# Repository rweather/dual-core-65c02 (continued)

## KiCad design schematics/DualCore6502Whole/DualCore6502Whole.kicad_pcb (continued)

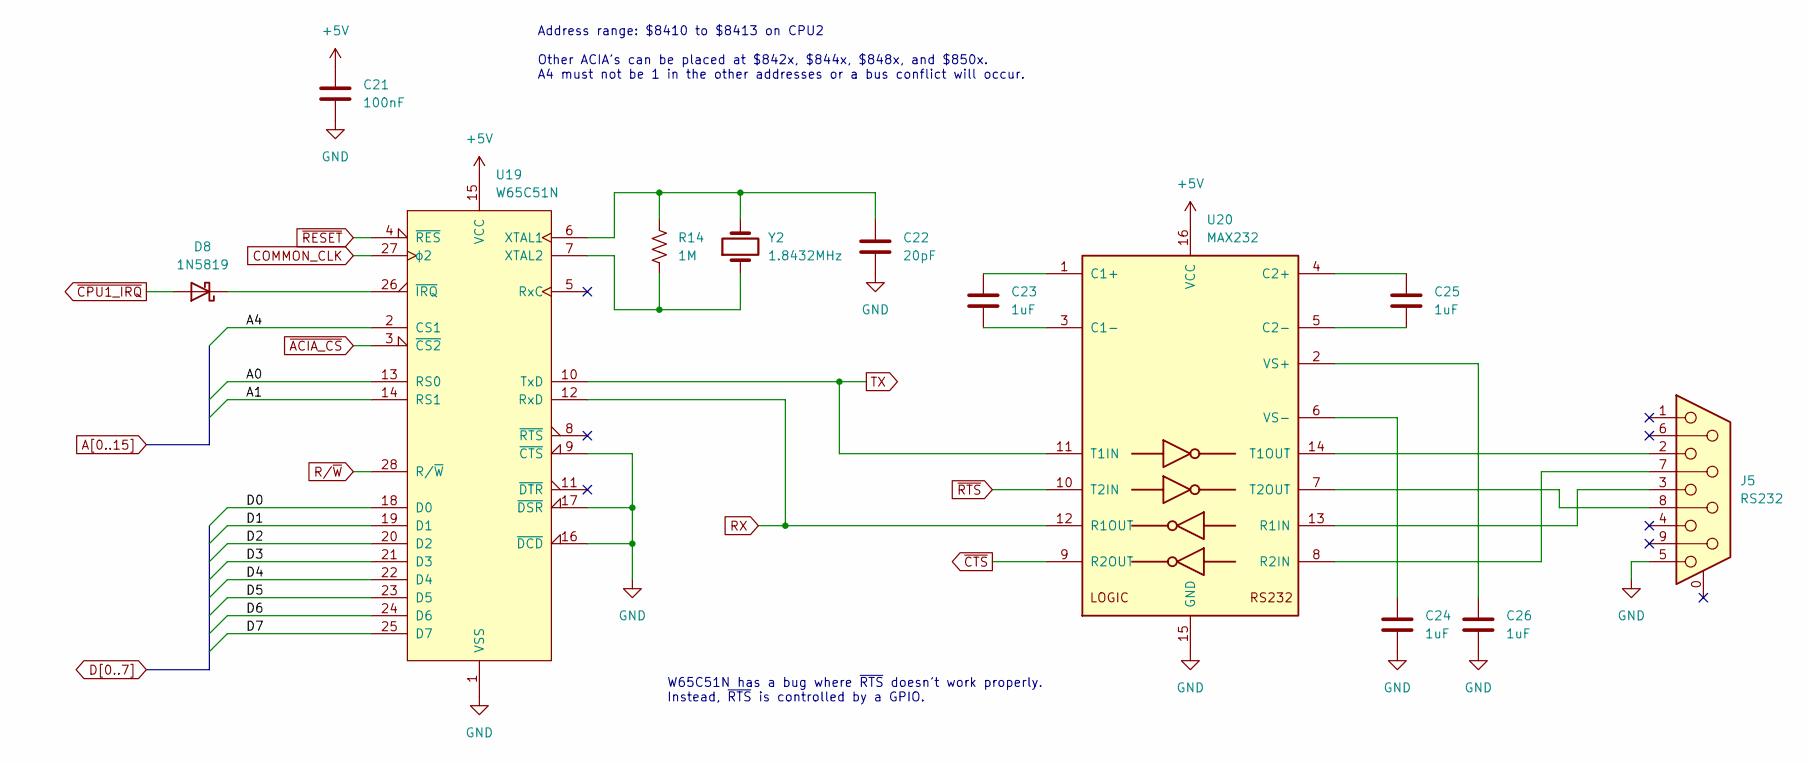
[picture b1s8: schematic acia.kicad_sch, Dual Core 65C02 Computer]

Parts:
C21: 100nF; C_Disc_D5.0mm_W2.5mm_P5.00mm
C22: 20pF; C_Disc_D5.0mm_W2.5mm_P5.00mm
C23, C24, C25, C26: 1uF; C_Disc_D5.0mm_W2.5mm_P5.00mm
D8: 1N5819; D_DO-41_SOD81_P10.16mm_Horizontal
J5: RS232; DSUB-9_Female_Horizontal_P2.77x2.84mm_EdgePinOffset4.94mm_H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
R14: 1M; R_Axial_DIN0207_L6.3mm_D2.5mm_P10.16mm_Horizontal
U19: W65C51N; DIP-28_W15.24mm_Socket
U20: MAX232; DIP-16_W7.62mm_Socket
Y2: 1.8432MHz; Crystal_HC49-U_Vertical

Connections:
+5V: C21.1, U19.15 (VCC), U20.16 (VCC); also elsewhere on the board
A0: U19.13 (RS0); also elsewhere on the board
A1: U19.14 (RS1); also elsewhere on the board
A4: U19.2 (CS1); also elsewhere on the board
COMMON_CLK: U19.27 (ϕ2); also elsewhere on the board
D0: U19.18 (D0); also elsewhere on the board
D1: U19.19 (D1); also elsewhere on the board
D2: U19.20 (D2); also elsewhere on the board
D3: U19.21 (D3); also elsewhere on the board
D4: U19.22 (D4); also elsewhere on the board
D5: U19.23 (D5); also elsewhere on the board
D6: U19.24 (D6); also elsewhere on the board
D7: U19.25 (D7); also elsewhere on the board
GND: C21.2, C22.2, C24.2, C26.2, J5.5, U19.1 (VSS), U19.9 (~CTS), U19.16 (~DCD), U19.17 (~DSR), U20.15 (GND); also elsewhere on the board
unnamed: D8.1 (K), U19.26 (~IRQ)
unnamed: C22.1, R14.1, U19.6 (XTAL1), Y2.2
unnamed: R14.2, U19.7 (XTAL2), Y2.1
unnamed: C23.1, U20.1 (C1+)
unnamed: C23.2, U20.3 (C1-)
unnamed: C25.1, U20.4 (C2+)
unnamed: C25.2, U20.5 (C2-)
unnamed: J5.3, U20.13 (R1IN)
unnamed: J5.7, U20.8 (R2IN)
unnamed: J5.2, U20.14 (T1OUT)
unnamed: J5.8, U20.7 (T2OUT)
unnamed: C26.1, U20.2 (VS+)
unnamed: C24.1, U20.6 (VS-)
RX: U19.12 (RxD), U20.12 (R1OUT); also elsewhere on the board
R/~W: U19.28 (R/~W); also elsewhere on the board
TX: U19.10 (TxD), U20.11 (T1IN); also elsewhere on the board
~ACIA_CS: U19.3 (~CS2); also elsewhere on the board
~CPU1_IRQ: D8.2 (A); also elsewhere on the board
~CTS: U20.9 (R2OUT); also elsewhere on the board
~RESET: U19.4 (~RES); also elsewhere on the board
~RTS: U20.10 (T2IN); also elsewhere on the board

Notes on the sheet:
W65C51N has a bug where ~{RTS} doesn't work properly. Instead, ~{RTS} is controlled by a GPIO.
Address range: $8410 to $8413 on CPU2 Other ACIA's can be placed at $842x, $844x, $848x, and $850x. A4 must not be 1 in the other addresses or a bus conflict will occur.

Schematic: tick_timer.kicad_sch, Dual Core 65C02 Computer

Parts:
C28: 10nF; C_Disc_D5.0mm_W2.5mm_P5.00mm
C29: 100nF; C_Disc_D5.0mm_W2.5mm_P5.00mm
JP2: NMI1; PinHeader_1x02_P2.54mm_Vertical
JP3: NMI2; PinHeader_1x02_P2.54mm_Vertical
R20: 5K6; R_Axial_DIN0207_L6.3mm_D2.5mm_P10.16mm_Horizontal
R21: 2K2; R_Axial_DIN0207_L6.3mm_D2.5mm_P10.16mm_Horizontal
RV1: 10K; Potentiometer_Bourns_3266Y_Vertical
TP7: 1KHz; TestPoint_Pad_D1.5mm
U4: 74HC02; DIP-14_W7.62mm_Socket
U22: 7555; DIP-8_W7.62mm_Socket

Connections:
+5V: R20.1, U22.8 (VCC); also elsewhere on the board
GND: C28.2, C29.2, U4.8, U4.12, U22.1 (GND); also elsewhere on the board
unnamed: JP2.1 (A), U4.13
unnamed: JP3.1 (A), U4.10
unnamed: R21.2, RV1.2
unnamed: C28.1, U22.5 (CV)
unnamed: R20.2, R21.1, U22.7 (DIS)
unnamed: TP7.1, U4.9, U4.11, U22.3 (Q)
unnamed: C29.1, RV1.3, U22.2 (TR), U22.6 (THR)
~CPU1_NMI: JP2.2 (B); also elsewhere on the board
~CPU2_NMI: JP3.2 (B); also elsewhere on the board
~RESET: U22.4 (R); also elsewhere on the board

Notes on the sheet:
Provides a 1ms signal to the CPU's for timing events when RV1 = 2K2
Invert so ~{CPUn_NMI} is pulled high during reset.

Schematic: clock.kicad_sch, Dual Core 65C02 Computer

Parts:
C5, C6, C7: 100nF; C_Disc_D5.0mm_W2.5mm_P5.00mm
U3: 74HC32; DIP-14_W7.62mm_Socket
U4: 74HC02; DIP-14_W7.62mm_Socket
U5: 74HC4017; DIP-16_W7.62mm_Socket
Y1: 12MHz; Oscillator_DIP-14

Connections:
+5V: C5.1, C6.1, C7.1, U3.14 (VCC), U4.14 (VCC), U5.16 (VDD), Y1.14 (Vcc); also elsewhere on the board
BUSEN_RESET: U4.2, U5.7 (Q3)
BUSEN_SET: U4.6, U5.3 (Q0)
COMMON_CLK: U3.11; also elsewhere on the board
CPU1_BUSEN: U4.1, U4.5; also elsewhere on the board
CPU1_CLK: U3.3; also elsewhere on the board
CPU1_CLK_RAW: U3.1, U3.13, U5.2 (Q1)
CPU2_BUSEN: U4.3, U4.4; also elsewhere on the board
CPU2_CLK: U3.8; also elsewhere on the board
CPU2_CLK_RAW: U3.10, U3.12, U5.10 (Q4)
GND: C5.2, C6.2, C7.2, U3.2, U3.4, U3.5, U3.7 (GND), U3.9, U4.7 (GND), U5.8 (VSS), U5.13 (CKEN), Y1.7 (GND); also elsewhere on the board
MAIN_CLK: U5.14 (CLK), Y1.8 (OUT); also elsewhere on the board
unnamed: U5.5 (Q6), U5.15 (Reset)

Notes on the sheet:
Raw CPU1_CLK and CPU2_CLK are delayed by one gate delay to match timing with COMMON_CLK.
MAIN_CLK
CPU2_CLK
COMMON_CLK
CPU2_BUSEN
MAIN_CLK (12MHz) is divided by 6 to create CPU1_CLK and CPU2_CLK (2MHz). Also divided by 6 to generate bus enables CPU1_BUSEN and CPU2_BUSEN. CPU1 can access the common bus only when CPU1_BUSEN is high and CPU2 can access the common bus only when CPU2_BUSEN is high. Bus enables are longer than cloc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
CPU1_CLK
CPU1_BUSEN

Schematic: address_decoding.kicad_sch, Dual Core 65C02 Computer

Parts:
C12, C13: 100nF; C_Disc_D5.0mm_W2.5mm_P5.00mm
U7: 74HC86; DIP-14_W7.62mm_Socket
U10: 74HC00; DIP-14_W7.62mm_Socket
U11: 74HC138; DIP-16_W7.62mm_Socket

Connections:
+5V: C12.1, C13.1, U7.2, U7.4, U10.13, U10.14 (VCC), U11.16 (VCC); also elsewhere on the board
A9: U11.1 (A0); also elsewhere on the board
A10: U11.2 (A1); also elsewhere on the board
A11: U11.3 (A2); also elsewhere on the board
A12: U11.4 (E1); also elsewhere on the board
A13: U11.5 (E2); also elsewhere on the board
A14: U7.1, U10.2; also elsewhere on the board
A15: U10.1, U10.4, U10.12; also elsewhere on the board
COMMON_CLK: U10.9; also elsewhere on the board
GND: C12.2, C13.2, U10.7 (GND), U11.8 (GND); also elsewhere on the board
IO_CS: U7.6, U11.6 (E3)
unnamed: U7.3, U10.5
unnamed: U7.5, U10.6
unnamed: U10.10, U10.11
~ACIA_CS: U11.13 (O2); also elsewhere on the board
~IORQ: U11.12 (O3); also elsewhere on the board
~IO_4_CS: U11.11 (O4); also elsewhere on the board
~IO_5_CS: U11.10 (O5); also elsewhere on the board
~IO_6_CS: U11.9 (O6); also elsewhere on the board
~IO_7_CS: U11.7 (O7); also elsewhere on the board
~MUTEX_CS: U11.15 (O0); also elsewhere on the board
~RAM_CS: U10.8; also elsewhere on the board
~ROM_CS: U10.3; also elsewhere on the board
~VIA_CS: U11.14 (O1); also elsewhere on the board

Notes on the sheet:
$8E00 - $8FFF
Memory Map: $0000 - $01FF - Zero page and stack for CPU1 $0200 - $03FF - Zero page and stack for CPU2 $0400 - $7FFF - Shared RAM $8000 - $8FFF - I/O Devices $9000 - $BFFF - Spare $C000 - $FFFF - This CPU's ROM
$8600 - $87FF
$8000 - $81FF
$8200 - $83FF
$8C00 - $8DFF
$8400 - $85FF
$8000 - $BFFF
$8800 - $89FF
$8A00 - $8BFF

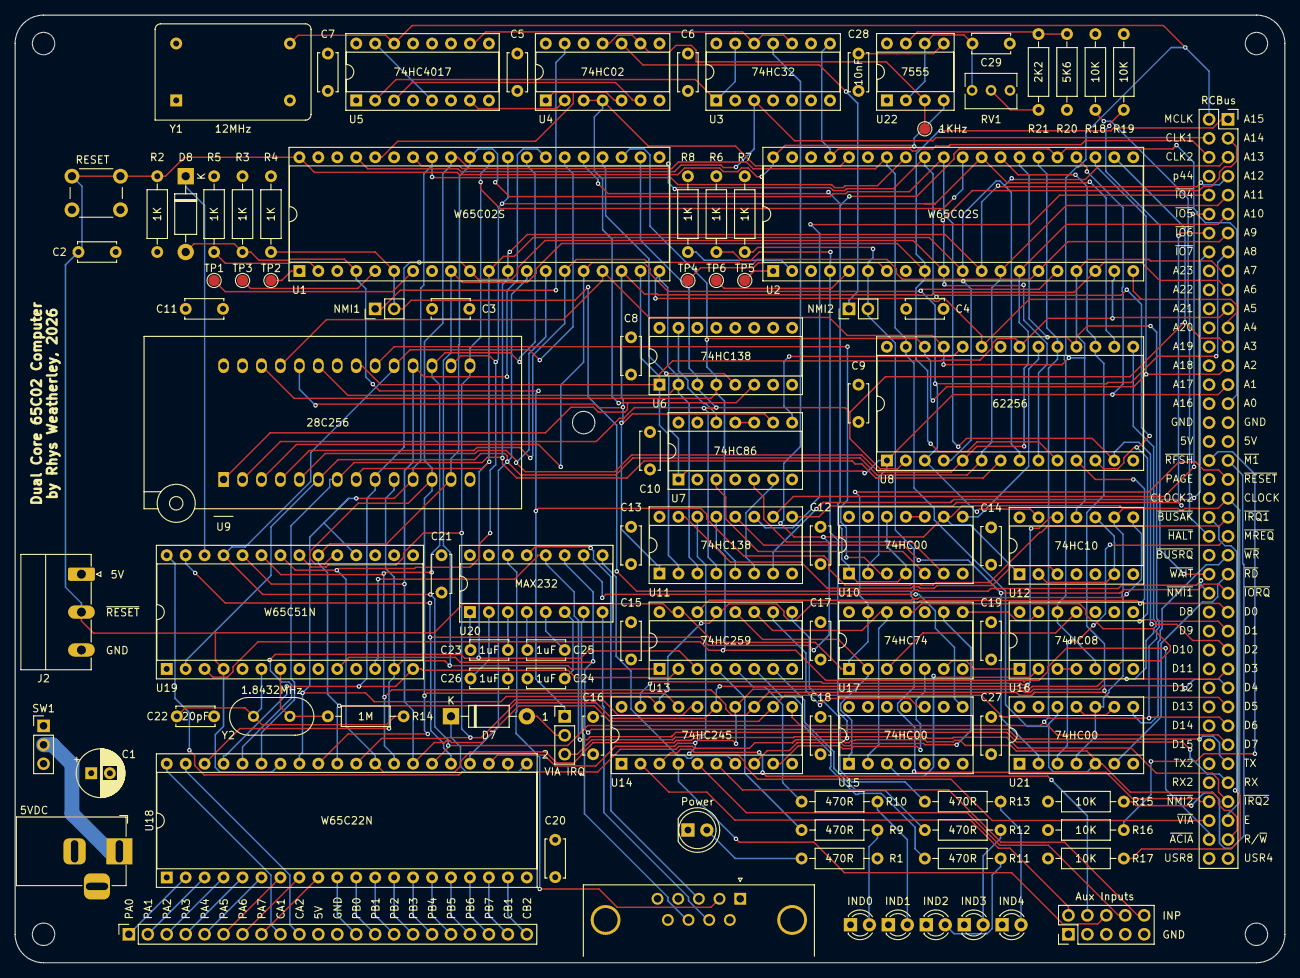
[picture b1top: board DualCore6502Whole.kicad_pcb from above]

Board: 4 copper layers, 170.2 x 127.0 mm, 106 parts (0 on the bottom side), 154 nets.

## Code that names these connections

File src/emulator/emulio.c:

/*
 * Copyright (C) 2026 Rhys Weatherley
 *
 * Permission is hereby granted, free of charge, to any person obtaining a
 * copy of this software and associated documentation files (the "Software"),
 * to deal in the Software without restriction, including without limitation
 * the rights to use, copy, modify, merge, publish, distribute, sublicense,
 * and/or sell copies of the Software, and to permit persons to whom the
 * Software is furnished to do so, subject to the following conditions:
 *
 * The above copyright notice and this permission notice shall be included
 * in all copies or substantial portions of the Software.
 *
 * THE SOFTWARE IS PROVIDED "AS IS", WITHOUT WARRANTY OF ANY KIND, EXPRESS
 * OR IMPLIED, INCLUDING BUT NOT LIMITED TO THE WARRANTIES OF MERCHANTABILITY,
 * FITNESS FOR A PARTICULAR PURPOSE AND NONINFRINGEMENT. IN NO EVENT SHALL THE
 * AUTHORS OR COPYRIGHT HOLDERS BE LIABLE FOR ANY CLAIM, DAMAGES OR OTHER
 * LIABILITY, WHETHER IN AN ACTION OF CONTRACT, TORT OR OTHERWISE, ARISING
 * FROM, OUT OF OR IN CONNECTION WITH THE SOFTWARE OR THE USE OR OTHER
 * DEALINGS IN THE SOFTWARE.
 */

#include "emulio.h"
#include <sys/ioctl.h>
#include <termios.h>
#include <unistd.h>
#include <poll.h>
#include <string.h>
#include <stdio.h>
#include <stdlib.h>
#include <errno.h>
#include <time.h>

/*
 * Locations in the I/O space between $8000 and $8FFF.
 */
#define INPUT_FLAGS 0x8080  /* Input flags */
#define RS232_RTS   0x8105  /* RTS signal to the RS-232 port */
#define MUTEX_WANT2 0x8106  /* Want the mutex on CPU2 */
#define MUTEX_WANT1 0x8107  /* Want the mutex on CPU1 */
#define ACIA_DATA   0x8410  /* ACIA data register */
#define ACIA_STATUS 0x8411  /* ACIA status register */
#define ACIA_CMD    0x8412  /* ACIA command register */
#define ACIA_CTRL   0x8413  /* ACIA control register */

/*
 * Input flags.
 */
#define FLAG_CTS    0x20    /* CTS signal from the RS-232 port */
#define FLAG_ACQ2   0x40    /* Acquired the mutex on CPU2 */
#define FLAG_ACQ1   0x80    /* Acquired the mutex on CPU1 */

/*
 * I/O flags in the emul6502_mem_t structure.
 */
#define IO_WANT1    0x0001  /* Want the mutex on CPU1 */
#define IO_WANT2    0x0002  /* Want the mutex on CPU2 */
#define IO_ACQ1     0x0004  /* Acquired the mutex on CPU1 */
#define IO_ACQ2     0x0008  /* Acquired the mutex on CPU2 */
#define IO_RTS      0x0010  /* RTS signal is raised, ACIA comms allowed */
#define IO_CTS      0x0020  /* CTS signal is lowered */

/*
 * Memory locations for the serial buffer in CPU1.
 */
#define SER_RD      0x00FC  /* Read pointer */
#define SER_WR      0x00FB  /* Write pointer */
#define SER_BUF     0x7F00  /* Serial receive buffer */

uint8_t emulio_load_byte(emul6502_t *emul, uint32_t addr)
{
    uint8_t result = 0;
    switch (addr) {
    case INPUT_FLAGS:
        if (emul->mem->io_flags & IO_ACQ1) {
            result |= FLAG_ACQ1;
        }
        if (emul->mem->io_flags & IO_ACQ2) {
            result |= FLAG_ACQ2;
        }
        if (emul->mem->io_flags & IO_CTS) {
            result |= FLAG_CTS;
        }
#if 0
        if (emul->cpu_num == 1) {
            /* Probably polling for the mutex on CPU1.  If we don't have it,
             * perform a small delay to avoid pegging the host CPU at 100% */
            if (!(emul->mem->io_flags & IO_ACQ1)) {
                usleep(1000);
            }
        } else {
            /* Same, but for CPU2 this time */
            if (!(emul->mem->io_flags & IO_ACQ2)) {
                usleep(1000);
            }
        }
#endif
        return result;

    default: break;
    }
    return 0;
}

void emulio_store_byte(emul6502_t *emul, uint32_t addr, uint8_t value)
{
    switch (addr) {
    case RS232_RTS:
        /* Raise or lower the RTS signal on the RS-232 port */
        if (value & 0x01) {
            emul->mem->io_flags |= IO_RTS;
        } else {
            emul->mem->io_flags &= ~IO_RTS;
        }
        break;

    case MUTEX_WANT1:
        /* CPU1 either wants the mutex or is releasing the mutex */
        if (value & 0x01) {
            emul->mem->io_flags |= IO_WANT1;
            if (!(emul->mem->io_flags & IO_ACQ2)) {
                emul->mem->io_flags |= IO_ACQ1;
            }
        } else {
            emul->mem->io_flags &= ~(IO_WANT1 | IO_ACQ1);
            if (emul->mem->io_flags & IO_WANT2) {
                emul->mem->io_flags |= IO_ACQ2;
            }
        }
        break;

    case MUTEX_WANT2:
        /* CPU2 either wants the mutex or is releasing the mutex */
        if (value & 0x01) {
            emul->mem->io_flags |= IO_WANT2;
            if (!(emul->mem->io_flags & IO_ACQ1)) {
                emul->mem->io_flags |= IO_ACQ2;
            }
        } else {
            emul->mem->io_flags &= ~(IO_WANT2 | IO_ACQ2);
            if (emul->mem->io_flags & IO_WANT1) {
                emul->mem->io_flags |= IO_ACQ1;
            }
        }
        break;

    case ACIA_DATA:
        /* Write to the serial port */
        emulio_tty_out(emul, value);
        break;

    case ACIA_STATUS:
    case ACIA_CMD:
    case ACIA_CTRL:
        /* Ignore ACIA setup as we assume we're running at full speed */
        break;

    default: break;
    }
}

static inline int emulio_tty_write_str(const char *str)
{
    int len = write(1, str, strlen(str));
    tcdrain(1);
    return len;
}

static inline int emulio_tty_write_ch(char ch)
{
    int len = write(1, &ch, 1);
    tcdrain(1);
    return len;
}

static struct termios orig_tio1, orig_tio2;

void emulio_tty_init(emul6502_t *emul)
{
    struct termios tio1, tio2;
    (void)emul;
    cfmakeraw(&orig_tio1);
    cfmakeraw(&orig_tio2);
    if (tcgetattr(0, &tio1) < 0 || tcgetattr(1, &tio2) < 0) {
        fprintf(stderr, "stdin and stdout must be a tty\n");
        exit(1);
    }
    orig_tio1 = tio1;
    orig_tio2 = tio2;
    cfmakeraw(&tio1);
    cfmakeraw(&tio2);
    tcsetattr(0, TCSANOW, &tio1);
    tcsetattr(1, TCSANOW, &tio2);

    /* Do we need to clear the screen at startup? */
    if (emul->cls) {
        /* Enter the alternate screen mode in xterm */
        emulio_tty_write_str("\x1B[?1047h");

        /* Set normal text mode by default and clear the screen */
        emulio_tty_write_str("\x1B[m\x1B[H\x1B[J");
    }
}

void emulio_tty_end(emul6502_t *emul)
{
    /* Return to normal text mode on shutdown */
    emulio_tty_write_str("\x1B[m");
    if (emul->cls) {
        /* Exit from the alternate screen mode */
        emulio_tty_write_str("\x1B[?1047l");
    }
    tcsetattr(0, TCSANOW, &orig_tio1);
    tcsetattr(1, TCSANOW, &orig_tio2);
}

void emulio_tty_out(emul6502_t *emul, uint8_t ch)
{
    (void)emul;
    /* Determine what to do with the character.  The only special
     * one we need to handle is CTRL-L / 0x0C for "clear screen". */
    if (ch == 0x0C)
        emulio_tty_write_str("\x1B[H\x1B[J");
    else
        emulio_tty_write_ch((char)ch);
}

int emulio_tty_in(emul6502_t *emul, int timeout)
{
    for (;;) {
        struct pollfd pfd = {
            .fd = 0,
            .events = POLLIN
        };
        int ret = poll(&pfd, 1, timeout);
        if (ret == 0) {
            return -1;
        } else if (ret > 0) {
            char ch = 0;
            if (read(0, &ch, 1) != 1)
                continue;
            if (ch == 0x11) {
                /* CTRL-Q - quit the emulator */
                emulio_tty_end(emul);
                if (!emul->cls)
                    printf("\n<QUIT>\n");
                exit(0);
            }
            if (ch >= 'a' && ch <= 'z' && !emul->lower) {
                /* Convert lower case to upper case on input */
                ch = ch - 'a' + 'A';
            }
            return ch & 0xFF;
        } else {
            if (errno != EAGAIN && errno != EINTR) {
                emulio_tty_end(emul);
                fprintf(stderr, "I/O failure\n");
                exit(1);
            }
        }
    }
    return -1;
}

void emulio_tty_peek(emul6502_t *emul)
{
    uint8_t write = emul->mem->memory[SER_RD];
    if (emul->mem->memory[SER_RD] == write) {
        /* Serial buffer is empty, so poll for keyboard input */
        int ch = emulio_tty_in(emul, 10);
        if (ch >= 0) {
            emul->mem->memory[SER_BUF + write] = (uint8_t)ch;
            emul->mem->memory[SER_WR] = (uint8_t)(write + 1);
        }
    }
}
